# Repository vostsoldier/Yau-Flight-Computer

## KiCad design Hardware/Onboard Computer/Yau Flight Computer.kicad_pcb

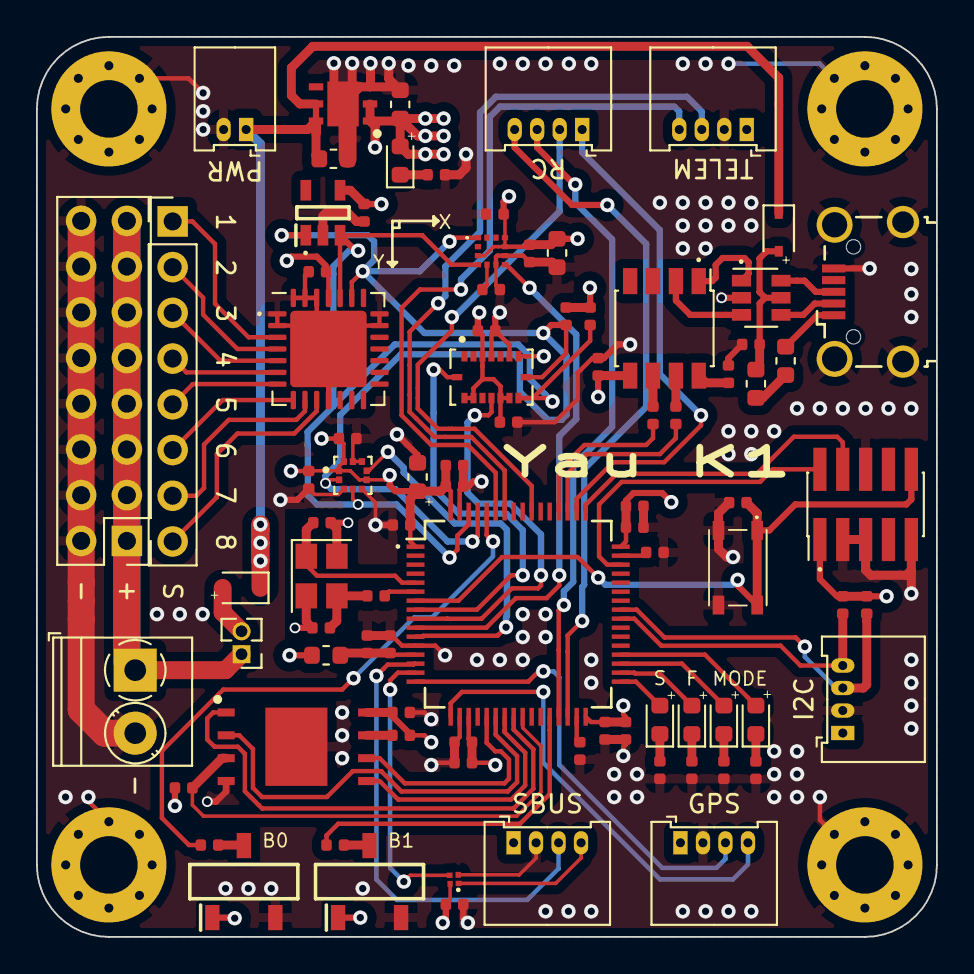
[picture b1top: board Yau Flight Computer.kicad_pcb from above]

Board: 4 copper layers, 50.0 x 50.0 mm, 6 parts (0 on the bottom side), 2 nets.

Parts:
GPS: Conn_01x04; Molex_PicoBlade_53048-0810_1x04_P1.25mm_Horizontal
I2C: Conn_01x04; Molex_PicoBlade_53048-0810_1x04_P1.25mm_Horizontal
PWR: Conn_01x02; Molex_PicoBlade_53048-0410_1x02_P1.25mm_Horizontal
SBUS: Conn_01x04; Molex_PicoBlade_53048-0810_1x04_P1.25mm_Horizontal
SWD: Conn_02x05_Counter_Clockwise; PinHeader_2x05_P1.27mm_Vertical_SMD
TELEM: Conn_01x04; Molex_PicoBlade_53048-0810_1x04_P1.25mm_Horizontal

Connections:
+3V3: GPS.1, I2C.1, SBUS.1, SWD.1, TELEM.1
GND: GPS.2, I2C.2, PWR.2, SBUS.2, SWD.3, SWD.5, SWD.6, SWD.9, TELEM.2

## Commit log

2025-06-13 Add journal entries for June 12th and 13th
2025-06-15 Added journal entries for June 14 and 15
2025-06-16 Add journal entries for June 16th
